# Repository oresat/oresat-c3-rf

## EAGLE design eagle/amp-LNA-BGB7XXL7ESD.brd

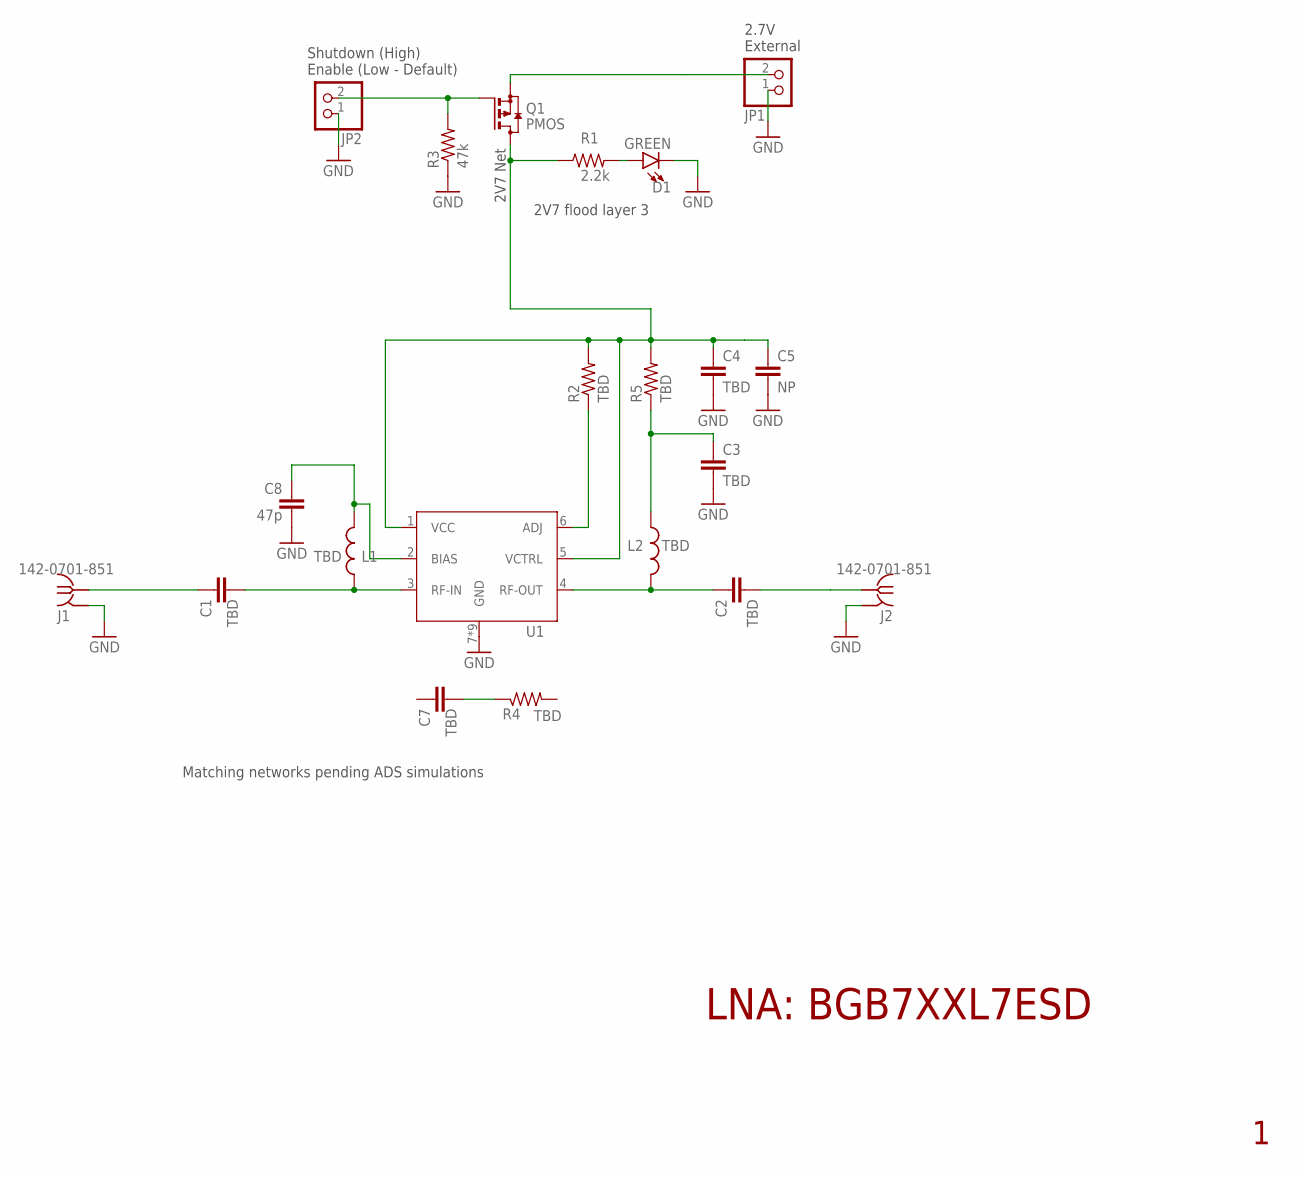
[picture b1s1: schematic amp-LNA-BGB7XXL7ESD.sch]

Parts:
C1, C2, C3, C4, C7: TBD; .0402-C-NOSILK
C5: NP; .0603-C-NOSILK
C8: 47p; .0402-C-NOSILK
D1: GREEN; LED-0603
J1, J2: 142-0701-851
JP1, JP2: PINHD-1X2; 1X02
L1, L2: TBD; .0402-C-NOSILK
Q1: PMOS; SOT23
R1: 2.2k; .0603-B-NOSILK
R2: TBD; .0603-B-NOSILK
R3: 47k; .0402-B-NOSILK
R4, R5: TBD; .0402-C-NOSILK
U1: BGB7XXL7ESD

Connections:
2V7: C4.1, C5.1, Q1.3 (D), R1.1, R2.2, R5.2, U1.1 (VCC), U1.5 (VCTRL)
GND: C3.2, C4.2, C5.2, C8.2, D1.C, J1.GND1 (GND), J1.GND2 (GND), J1.GND3 (GND), J1.GND4 (GND), J2.GND1 (GND), J2.GND2 (GND), J2.GND3 (GND), J2.GND4 (GND), JP1.1, JP2.1, R3.1, U1.7 (GND), U1.8 (GND), U1.9 (GND), U1.10 (GND), U1.11 (GND), U1.12 (GND), U1.13 (GND), U1.14 (GND), U1.15 (GND)
unnamed: JP2.2, Q1.1 (G), R3.2
unnamed: C3.1, L2.1, R5.1
unnamed: C2.1, L2.2, U1.4 (RF-OUT)
unnamed: R2.1, U1.6 (ADJ)
unnamed: C8.1, L1.2, U1.2 (BIAS)
unnamed: C1.1, J1.RF1 (RF)
unnamed: C7.2, R4.1
unnamed: D1.A, R1.2
unnamed: C1.2, L1.1, U1.3 (RF-IN)
RF_OUT: C2.2, J2.RF1 (RF)
VEXT: JP1.2, Q1.2 (S)

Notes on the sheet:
LNA: BGB7XXL7ESD
2.7V External
Shutdown (High) Enable (Low - Default)
Matching networks pending ADS simulations
2V7 flood layer 3
2V7 Net

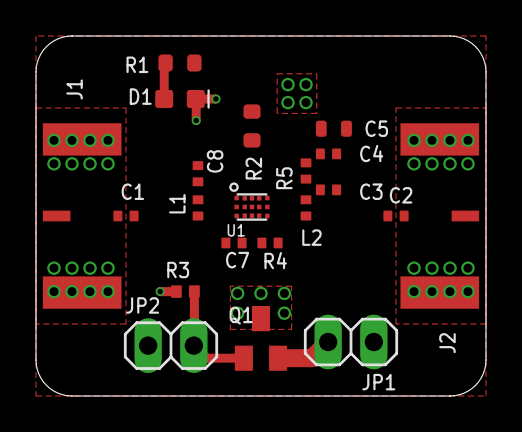
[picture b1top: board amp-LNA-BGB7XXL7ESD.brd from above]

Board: 4 copper layers, 25.0 x 20.0 mm, 21 parts (0 on the bottom side), 13 nets.

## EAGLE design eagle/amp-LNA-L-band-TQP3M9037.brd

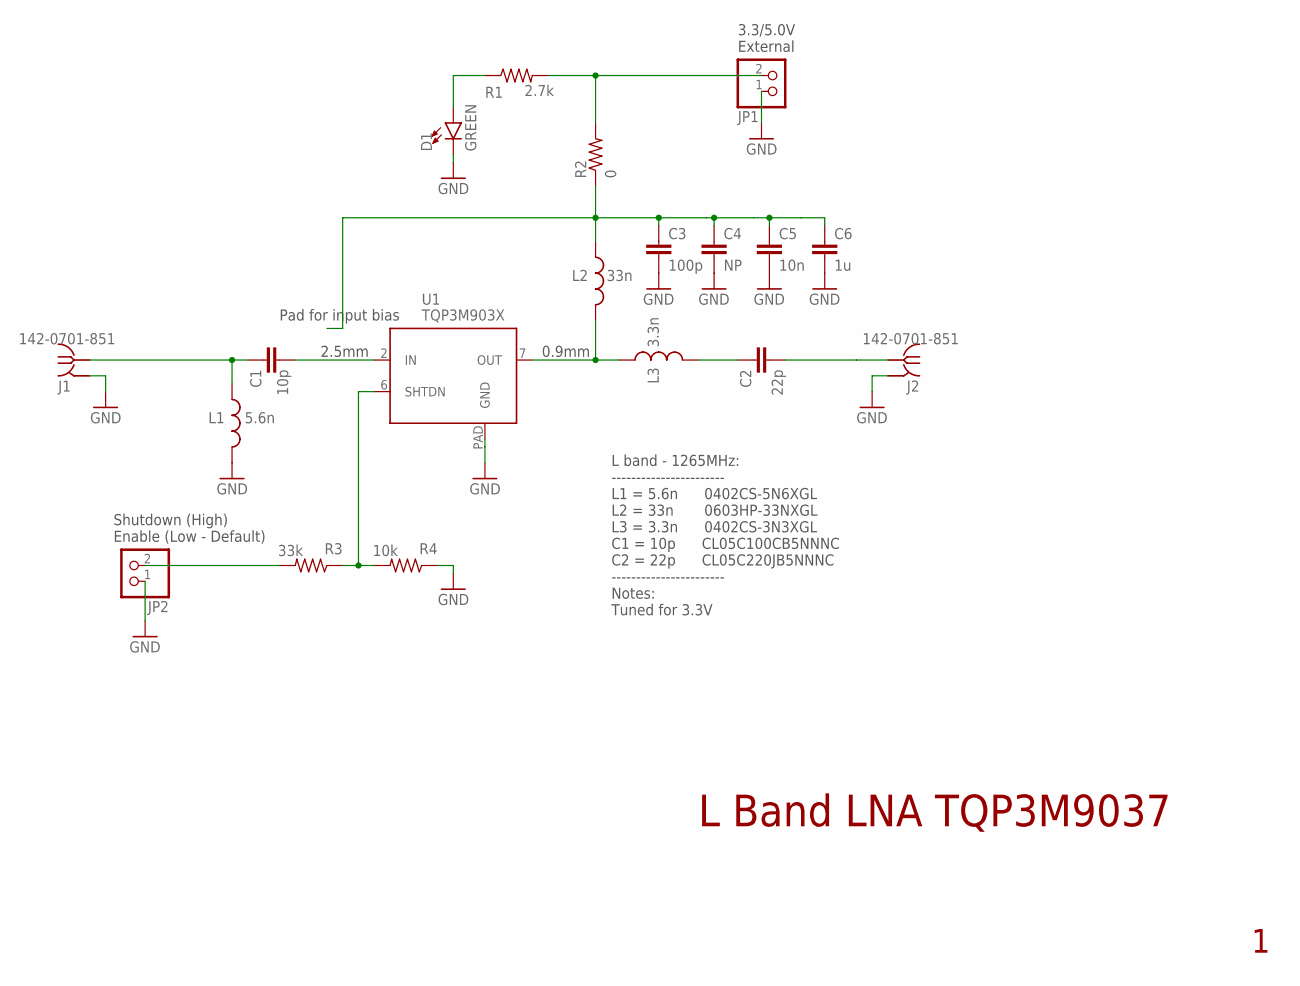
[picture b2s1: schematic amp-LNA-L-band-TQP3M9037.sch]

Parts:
C1: 10p; .0402-C-NOSILK
C2: 22p; .0402-C-NOSILK
C3: 100p; .0603-B-NOSILK
C4: NP; .0603-B-NOSILK
C5: 10n; .0603-B-NOSILK
C6: 1u; .0603-B-NOSILK
D1: GREEN; LED-0603
J1, J2: 142-0701-851
JP1, JP2: PINHD-1X2; 1X02
L1: 5.6n; .0402-C-NOSILK
L2: 33n; .0603-C-NOSILK
L3: 3.3n; .0402-C-NOSILK
R1: 2.7k; .0603-B-NOSILK
R2: 0; .0603-B-NOSILK
R3: 33k; .0603-B-NOSILK
R4: 10k; .0603-B-NOSILK
U1: TQP3M903X; DFN8-2X2-WITH-PAD

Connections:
GND: C3.2, C4.2, C5.2, C6.2, D1.C, J1.GND1 (GND), J1.GND2 (GND), J1.GND3 (GND), J1.GND4 (GND), J2.GND1 (GND), J2.GND2 (GND), J2.GND3 (GND), J2.GND4 (GND), JP1.1, JP2.1, L1.2, R4.1, U1.PAD (GND)
unnamed: JP1.2, R1.2, R2.2
unnamed: R3.1, R4.2, U1.6 (SHTDN)
unnamed: JP2.2, R3.2
unnamed: C1.2, U1.2 (IN)
unnamed: C2.1, L3.2
unnamed: D1.A, R1.1
unnamed: L2.2, L3.1, U1.7 (OUT)
unnamed: C3.1, C4.1, C5.1, C6.1, L2.1, R2.1
RF_IN: C1.1, J1.RF1 (RF), L1.1
RF_OUT: C2.2, J2.RF1 (RF)

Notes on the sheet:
L Band LNA TQP3M9037
L band - 1265MHz: ----------------------- L1 = 5.6n 0402CS-5N6XGL L2 = 33n 0603HP-33NXGL L3 = 3.3n 0402CS-3N3XGL C1 = 10p CL05C100CB5NNNC C2 = 22p CL05C220JB5NNNC ----------------------- Notes: Tuned for 3.3V
Shutdown (High) Enable (Low - Default)
3.3/5.0V External
Pad for input bias
2.5mm
0.9mm

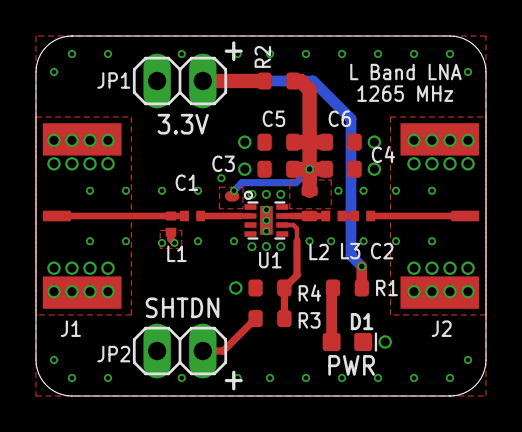
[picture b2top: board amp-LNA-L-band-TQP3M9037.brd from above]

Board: 4 copper layers, 25.0 x 20.0 mm, 19 parts (0 on the bottom side), 11 nets.

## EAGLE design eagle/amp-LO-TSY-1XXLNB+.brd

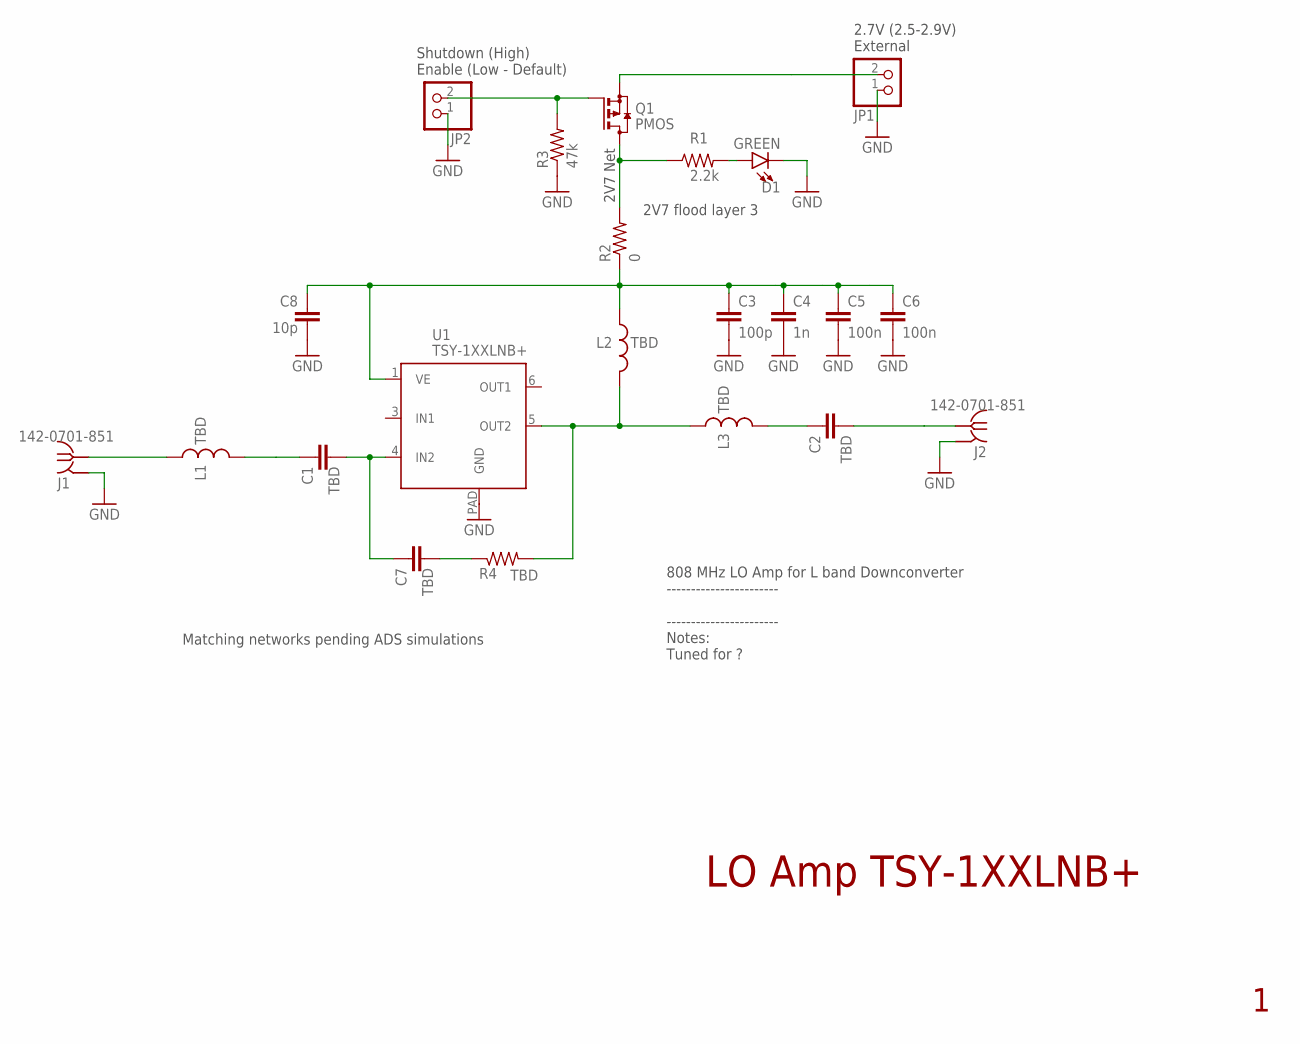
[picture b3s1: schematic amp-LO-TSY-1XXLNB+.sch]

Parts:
C1, C2, C7: TBD; .0402-C-NOSILK
C3: 100p; .0603-B-NOSILK
C4: 1n; .0603-B-NOSILK
C5, C6: 100n; .0603-B-NOSILK
C8: 10p; .0402-C-NOSILK
D1: GREEN; LED-0603
J1, J2: 142-0701-851
JP1, JP2: PINHD-1X2; 1X02
L1, L3: TBD; .0402-C-NOSILK
L2: TBD; .0603-C-NOSILK
Q1: PMOS; SOT23
R1: 2.2k; .0603-B-NOSILK
R2: 0; .0603-B-NOSILK
R3: 47k; .0402-B-NOSILK
R4: TBD; .0402-B-NOSILK
U1: TSY-1XXLNB+; MCLP8-2X2-WITH-PAD

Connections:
2V7: Q1.3 (D), R1.1, R2.2
GND: C3.2, C4.2, C5.2, C6.2, C8.2, D1.C, J1.GND1 (GND), J1.GND2 (GND), J1.GND3 (GND), J1.GND4 (GND), J2.GND1 (GND), J2.GND2 (GND), J2.GND3 (GND), J2.GND4 (GND), JP1.1, JP2.1, R3.1, U1.PAD (GND)
IN: C1.2, C7.1, U1.4 (IN2)
unnamed: JP2.2, Q1.1 (G), R3.2
unnamed: C2.1, L3.2
unnamed: C1.1, L1.2
unnamed: C7.2, R4.1
unnamed: D1.A, R1.2
unnamed: J1.RF1 (RF), L1.1
OUT: L2.2, L3.1, R4.2, U1.5 (OUT2)
RF_OUT: C2.2, J2.RF1 (RF)
VE: C3.1, C4.1, C5.1, C6.1, C8.1, L2.1, R2.1, U1.1 (VE)
VEXT: JP1.2, Q1.2 (S)

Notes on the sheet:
LO Amp TSY-1XXLNB+
808 MHz LO Amp for L band Downconverter ----------------------- ----------------------- Notes: Tuned for ?
2.7V (2.5-2.9V) External
Shutdown (High) Enable (Low - Default)
Matching networks pending ADS simulations
2V7 flood layer 3
2V7 Net

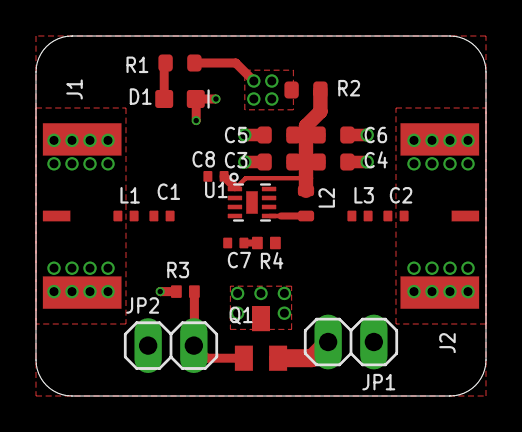
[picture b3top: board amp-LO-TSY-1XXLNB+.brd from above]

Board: 4 copper layers, 25.0 x 20.0 mm, 22 parts (0 on the bottom side), 13 nets.

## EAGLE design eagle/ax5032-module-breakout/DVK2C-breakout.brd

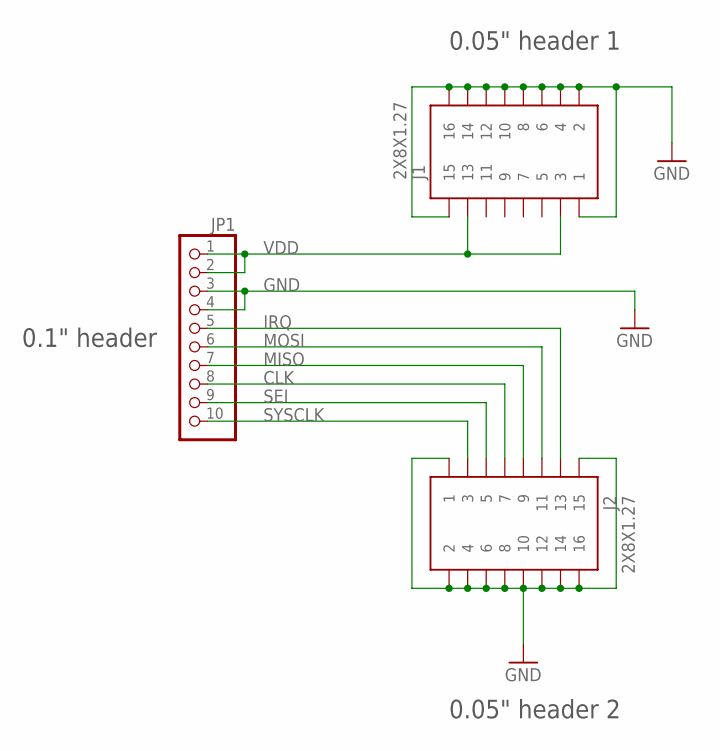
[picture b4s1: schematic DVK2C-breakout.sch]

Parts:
J1, J2: 2X8X1.27
JP1: PINHD-1X10; 1X10

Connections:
CLK: J2.7, JP1.8
GND: J1.1, J1.2, J1.4, J1.6, J1.8, J1.10, J1.12, J1.14, J1.15, J1.16, J2.1, J2.2, J2.4, J2.6, J2.8, J2.10, J2.12, J2.14, J2.15, J2.16, JP1.3, JP1.4
IRQ: J2.13, JP1.5
MISO: J2.9, JP1.7
MOSI: J2.11, JP1.6
SEI: J2.5, JP1.9
SYSCLK: J2.3, JP1.10
VDD: J1.3, J1.13, JP1.1, JP1.2

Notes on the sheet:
0.1" header
0.05" header 1
0.05" header 2

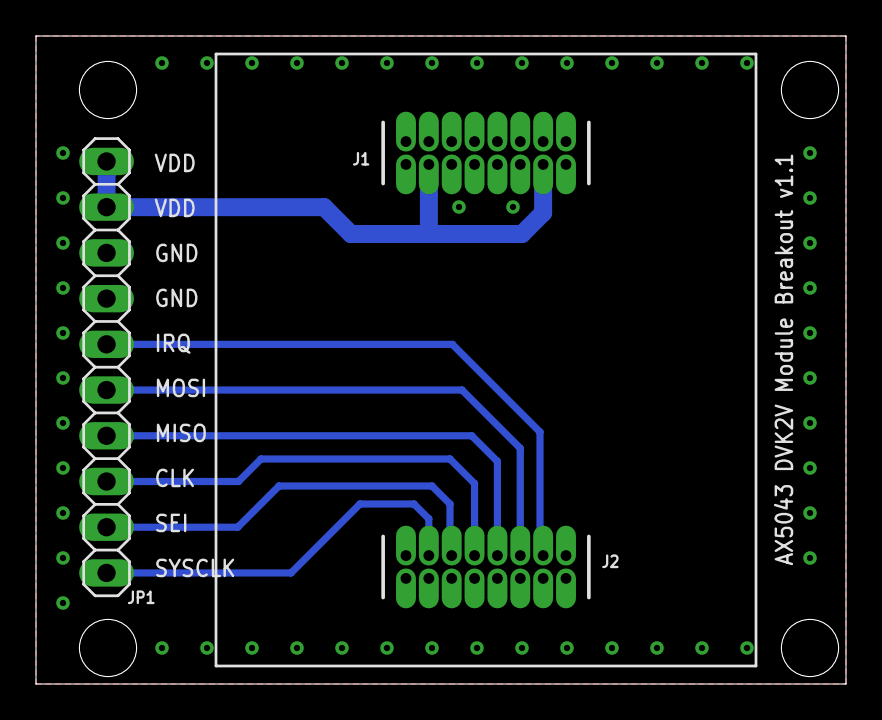
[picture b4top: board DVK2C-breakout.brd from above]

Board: 2 copper layers, 45.0 x 36.0 mm, 3 parts (0 on the bottom side), 8 nets.

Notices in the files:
parts and their libraries:
SparkFun-LED: Licensing: Creative Commons ShareAlike 4.0 International - https://creativecommons.org/licenses/by-sa/4.0
